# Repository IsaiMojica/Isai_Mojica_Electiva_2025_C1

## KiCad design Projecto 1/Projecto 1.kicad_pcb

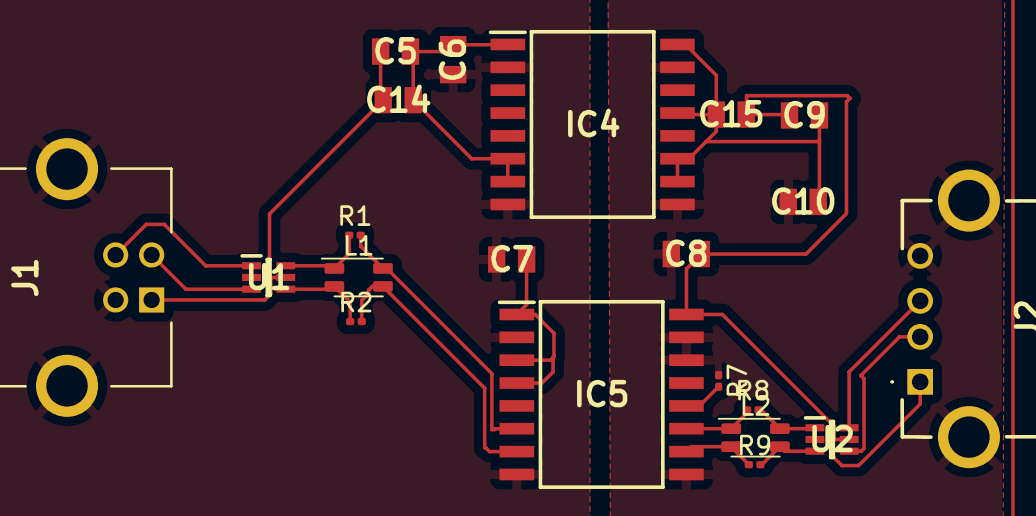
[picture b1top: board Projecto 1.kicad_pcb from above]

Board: 2 copper layers, 21 parts (0 on the bottom side), 19 nets.

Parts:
C5, C9: GRM21BR61C106KE15L; CAPC2012X145N
C6, C7, C8, C10, C14, C15: GRM21BR71H104KA01L; CAPC2012X145N
IC4: ADUM5000ARWZ; SOIC127P1032X265-16N
IC5: ADUM4160BRWZ; SOIC127P1032X265-16N
J1: USB-B-S-F-B-TH-R; USBBSFBTHR
J2: 87520-0010BLF; 875200010BLF
L1, L2: Choke_Wurth_WE-CNSW_744232090; L_CommonMode_Wurth_WE-CNSW-1206
R1, R2, R7, R8, R9: R; R_0201_0603Metric
U1, U2: USBLC6-2SC6; SOT65P210X110-6N

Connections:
+5V: C5.1, C7.2, C14.2, IC5.1 (VBUS1), IC5.3 (VDD1), IC5.4 (PDEN), J1.1, U1.5 (VBUS)
GND: C6.2, C7.1, IC4.2 (GND1_1), IC4.8 (GND1_2), IC5.2 (GND1_1), IC5.8 (GND1_2), J1.4, J1.MH1, J1.MH2, U1.2 (GND)
GND2: C8.1, C10.1, IC4.9 (GNDISO_1), IC4.15 (GNDISO_2), IC5.9 (GND2_1), IC5.14 (VDD2), IC5.15 (GND2_2), J2.4, J2.MH1, J2.MH2, R7.1, U2.2 (GND)
unnamed: C9.2, C10.2, C15.1, IC4.10 (VISO_1), IC4.11 (NC_2), IC4.13 (VSEL), IC4.16 (VISO_2)
unnamed: C5.2, C6.1, C14.1, IC4.1 (VDD1_1), IC4.6 (RCSEL), IC4.7 (VDD1_2)
unnamed: IC5.10 (DD+), L2.4, R9.1
unnamed: IC5.11 (DD-), L2.1, R8.1
unnamed: IC5.12 (PIN), R7.2
unnamed: IC5.7 (UD+), L1.3, R2.2
unnamed: IC5.6 (UD-), L1.2, R1.2
unnamed: J1.2, U1.3 (I/O2)
unnamed: J1.3, U1.1 (I/O1)
unnamed: J2.2, U2.4 (I/O2)
unnamed: J2.3, U2.6 (I/O1)
unnamed: L1.1, R1.1, U1.6 (I/O1)
unnamed: L1.4, R2.1, U1.4 (I/O2)
unnamed: L2.2, R8.2, U2.1 (I/O1)
unnamed: L2.3, R9.2, U2.3 (I/O2)
VDD: C8.2, C9.1, C15.2, IC5.16 (VBUS2), J2.1, U2.5 (VBUS)

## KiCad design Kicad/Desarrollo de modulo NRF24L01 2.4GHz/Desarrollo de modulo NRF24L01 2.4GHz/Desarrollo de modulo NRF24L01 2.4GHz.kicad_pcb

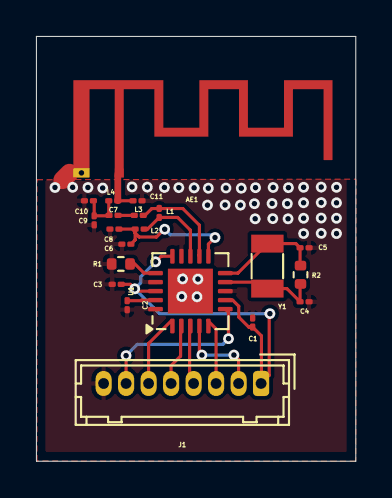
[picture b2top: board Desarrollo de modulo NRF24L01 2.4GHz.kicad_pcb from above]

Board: 2 copper layers, 17.7 x 23.6 mm, 21 parts (0 on the bottom side), 18 nets.

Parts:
AE1: Antenna; Texas_SWRA117D_2.4GHz_Right
C1: 10n; C_01005_0402Metric
C2: 33n; C_01005_0402Metric
C3: 1n; C_01005_0402Metric
C4, C5: 22p; C_01005_0402Metric
C6, C8: C_Small; C_01005_0402Metric
C7: 1n5; C_01005_0402Metric
C9: 1p; C_01005_0402Metric
C10, C11: Cx; C_01005_0402Metric
J1: Conn_01x08_Pin; Hirose_DF13-08P-1.25DSA_1x08_P1.25mm_Vertical
L1: 8n2; L_01005_0402Metric
L2: 2n7; L_01005_0402Metric
L3: 3n9; L_01005_0402Metric
L4: Lx; L_01005_0402Metric
R1: 22K; R_0402_1005Metric
R2: 10M; R_0402_1005Metric
U1: nRF24L01P; QFN-20-1EP_4x4mm_P0.5mm_EP2.5x2.5mm
Y1: 16MHz; Crystal_SMD_3215-2Pin_3.2x1.5mm

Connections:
GND: C1.2, C2.2, C3.2, C4.2, C5.2, C6.2, C8.2, C9.2, C10.2, C11.2, J1.8, R1.2, U1.8 (VSS), U1.14 (VSS), U1.17 (VSS), U1.20 (VSS)
unnamed: AE1.1 (A), C11.1, L4.2
unnamed: C7.1, L3.2
unnamed: C7.2, C9.1, C10.1, L4.1
unnamed: J1.2, U1.4 (MOSI)
unnamed: J1.3, U1.5 (MISO)
unnamed: J1.4, U1.3 (SCK)
unnamed: J1.5, U1.2 (CSN)
unnamed: J1.6, U1.1 (CE)
unnamed: J1.7, U1.6 (IRQ)
unnamed: L1.1, L3.1, U1.12 (ANT1)
unnamed: L1.2, L2.1, U1.13 (ANT2)
unnamed: C2.1, U1.19 (DVDD)
unnamed: R1.1, U1.16 (IREF)
unnamed: C6.1, C8.1, L2.2, U1.11 (VDD_PA)
unnamed: C5.1, R2.2, U1.10 (XC1), Y1.2
unnamed: C4.1, R2.1, U1.9 (XC2), Y1.1
VDD: C1.1, C3.1, J1.1, U1.7 (VDD), U1.15 (VDD), U1.18 (VDD)
